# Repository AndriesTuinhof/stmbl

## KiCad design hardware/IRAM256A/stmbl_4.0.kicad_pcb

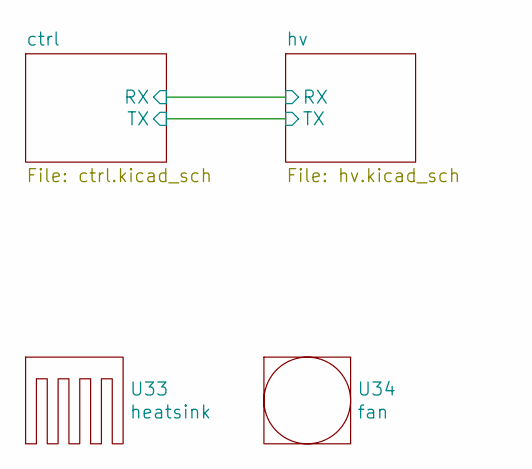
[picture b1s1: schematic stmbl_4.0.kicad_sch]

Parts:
U33: heatsink
U34: fan; Voltage 12V

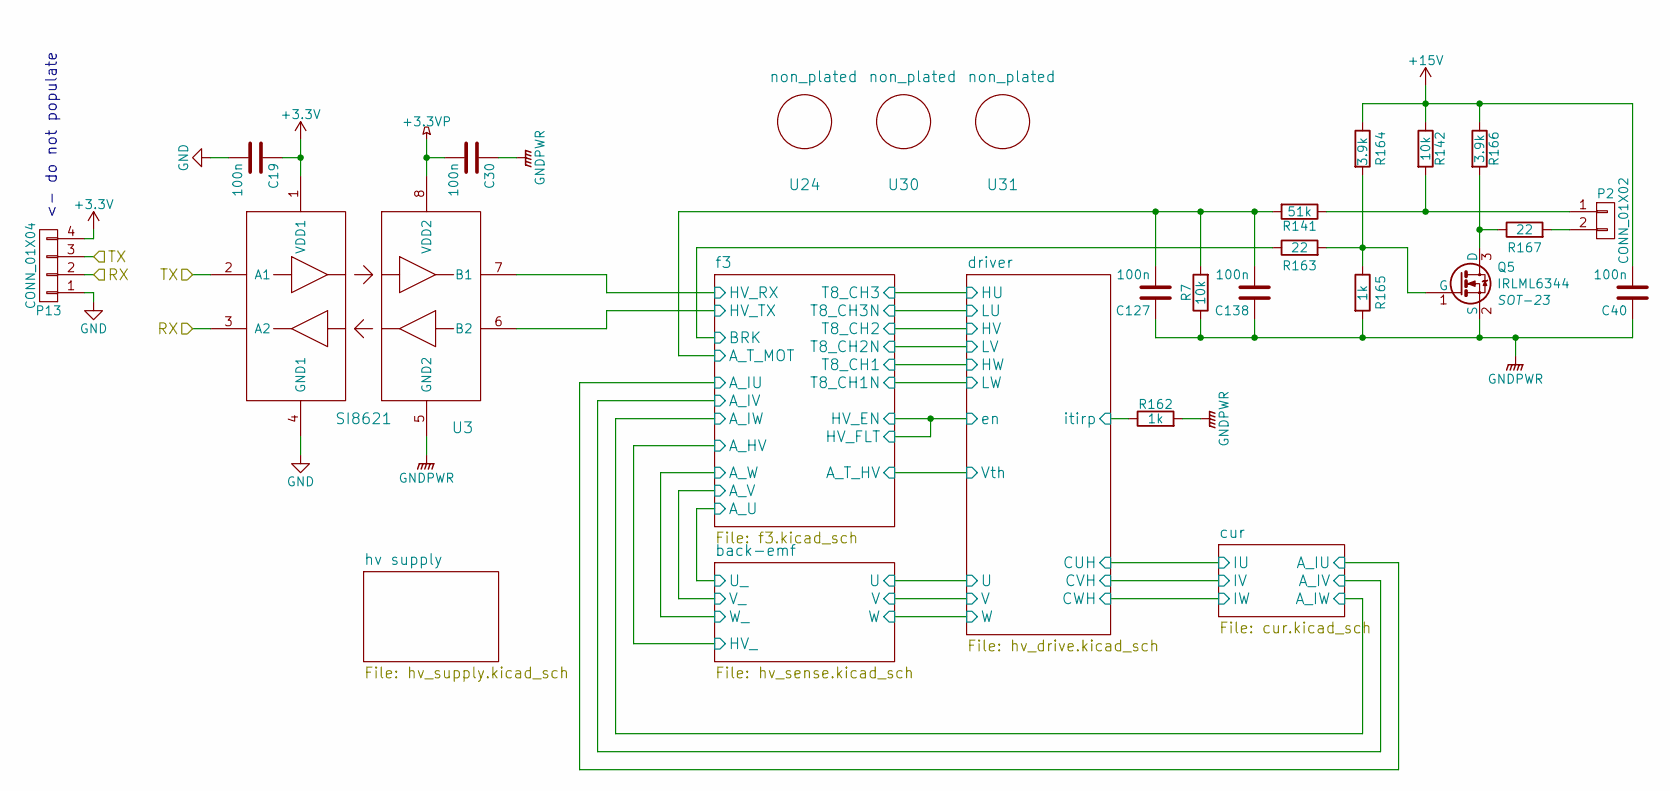
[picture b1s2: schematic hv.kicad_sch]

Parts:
C19, C30, C40, C127, C138: 100n; C_0603; Voltage 50V; Tolerance X5R
P2: CONN_01X02; RM3.5_1x2
P13: CONN_01X04; Socket_Strip_Straight_1x04
Q5: IRLML6344; SOT-23
R7, R142: 10k; R_0603; Tolerance 1%
R141: 51k; R_0603; Tolerance 1%
R162, R165: 1k; R_0603; Tolerance 1%
R163, R167: 22; R_0603; Tolerance 1%
R164, R166: 3.9k; R_0603; Tolerance 1%
U3: SI8621; SOIC-8-N
U24, U30, U31: non_plated; non_plated_3mm

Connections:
+3.3VP: C30.2, U3.8 (VDD2); also elsewhere on the board
+3V3: C19.1, P13.4, U3.1 (VDD1); also elsewhere on the board
+15V: C40.2, R142.1, R164.1, R166.1; also elsewhere on the board
/ctrl/RX: P13.2, U3.3 (A2); also elsewhere on the board
/ctrl/TX: P13.3, U3.2 (A1); also elsewhere on the board
/hv/driver/itirp: R162.1; also elsewhere on the board
/hv/f3/A_T_MOT: C127.2, C138.2, R7.2, R141.2; also elsewhere on the board
/hv/f3/BRK: R163.1; also elsewhere on the board
/hv/f3/HV_RX: U3.7 (B1); also elsewhere on the board
/hv/f3/HV_TX: U3.6 (B2); also elsewhere on the board
GND: C19.2, P13.1, U3.4 (GND1); also elsewhere on the board
GNDPWR: C30.1, C40.1, C127.1, C138.1, Q5.2 (S), R7.1, R162.2, R165.2, U3.5 (GND2); also elsewhere on the board
unnamed: P2.1, R141.1, R142.2
unnamed: P2.2, R167.2
unnamed: Q5.1 (G), R163.2, R164.2, R165.1
unnamed: Q5.3 (D), R166.2, R167.1

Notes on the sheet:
<- do not populate

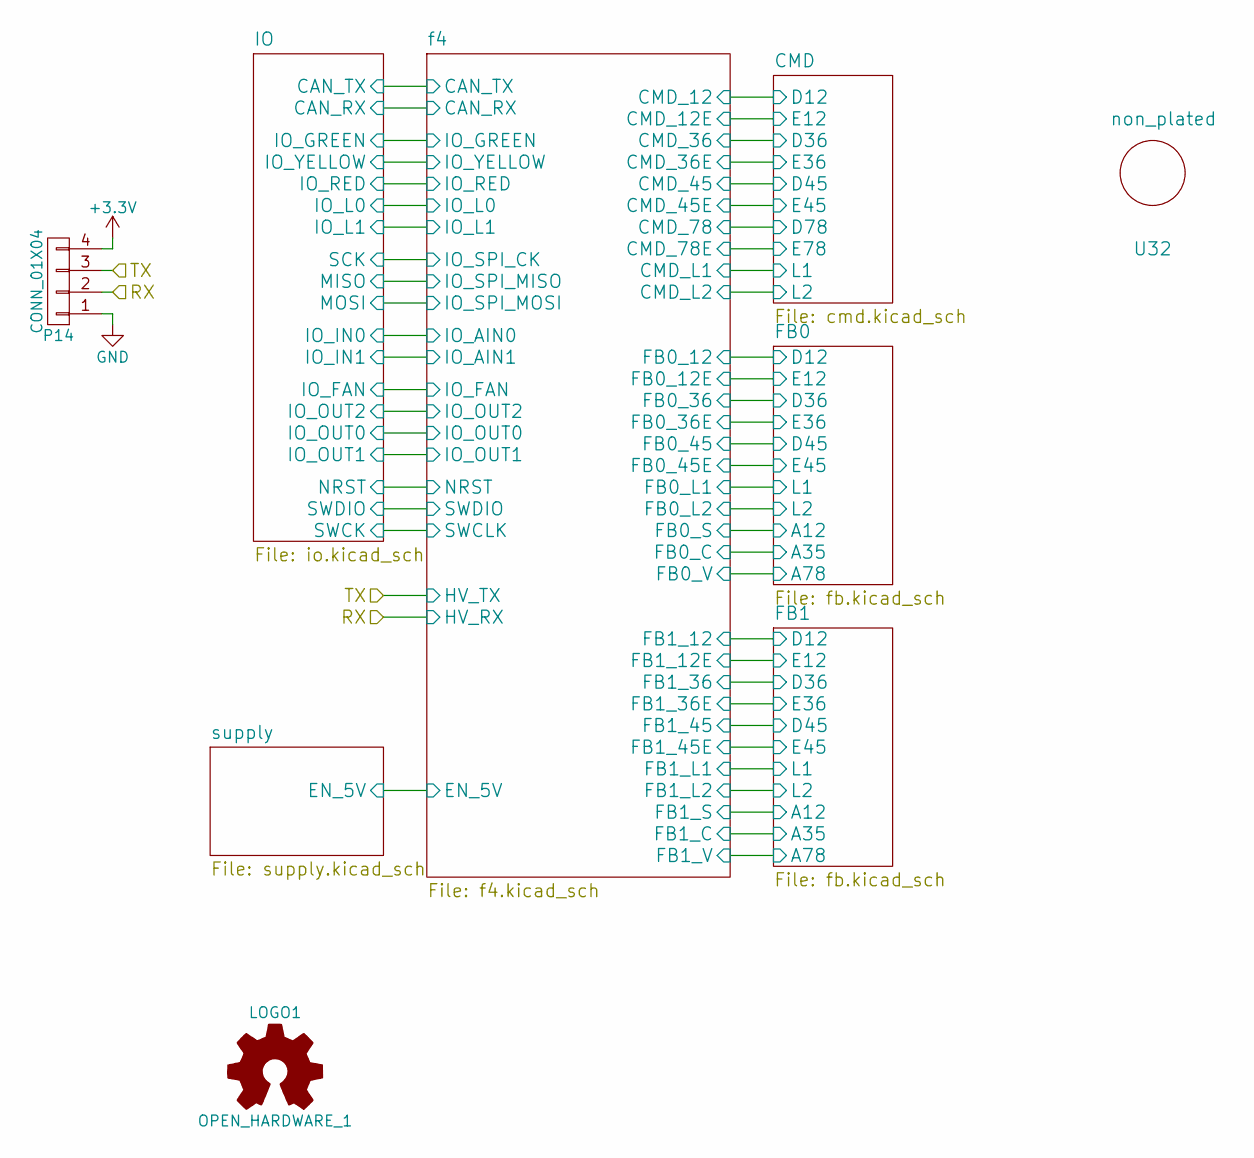
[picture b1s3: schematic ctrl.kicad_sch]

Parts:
LOGO1: OPEN_HARDWARE_1; Symbol_OSHW-Logo_SilkScreen
P14: CONN_01X04; Pin_Header_Angled_1x04
U32: non_plated; non_plated_3mm

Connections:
+3V3: P14.4; also elsewhere on the board
/ctrl/RX: P14.2; also elsewhere on the board
/ctrl/TX: P14.3; also elsewhere on the board
GND: P14.1; also elsewhere on the board

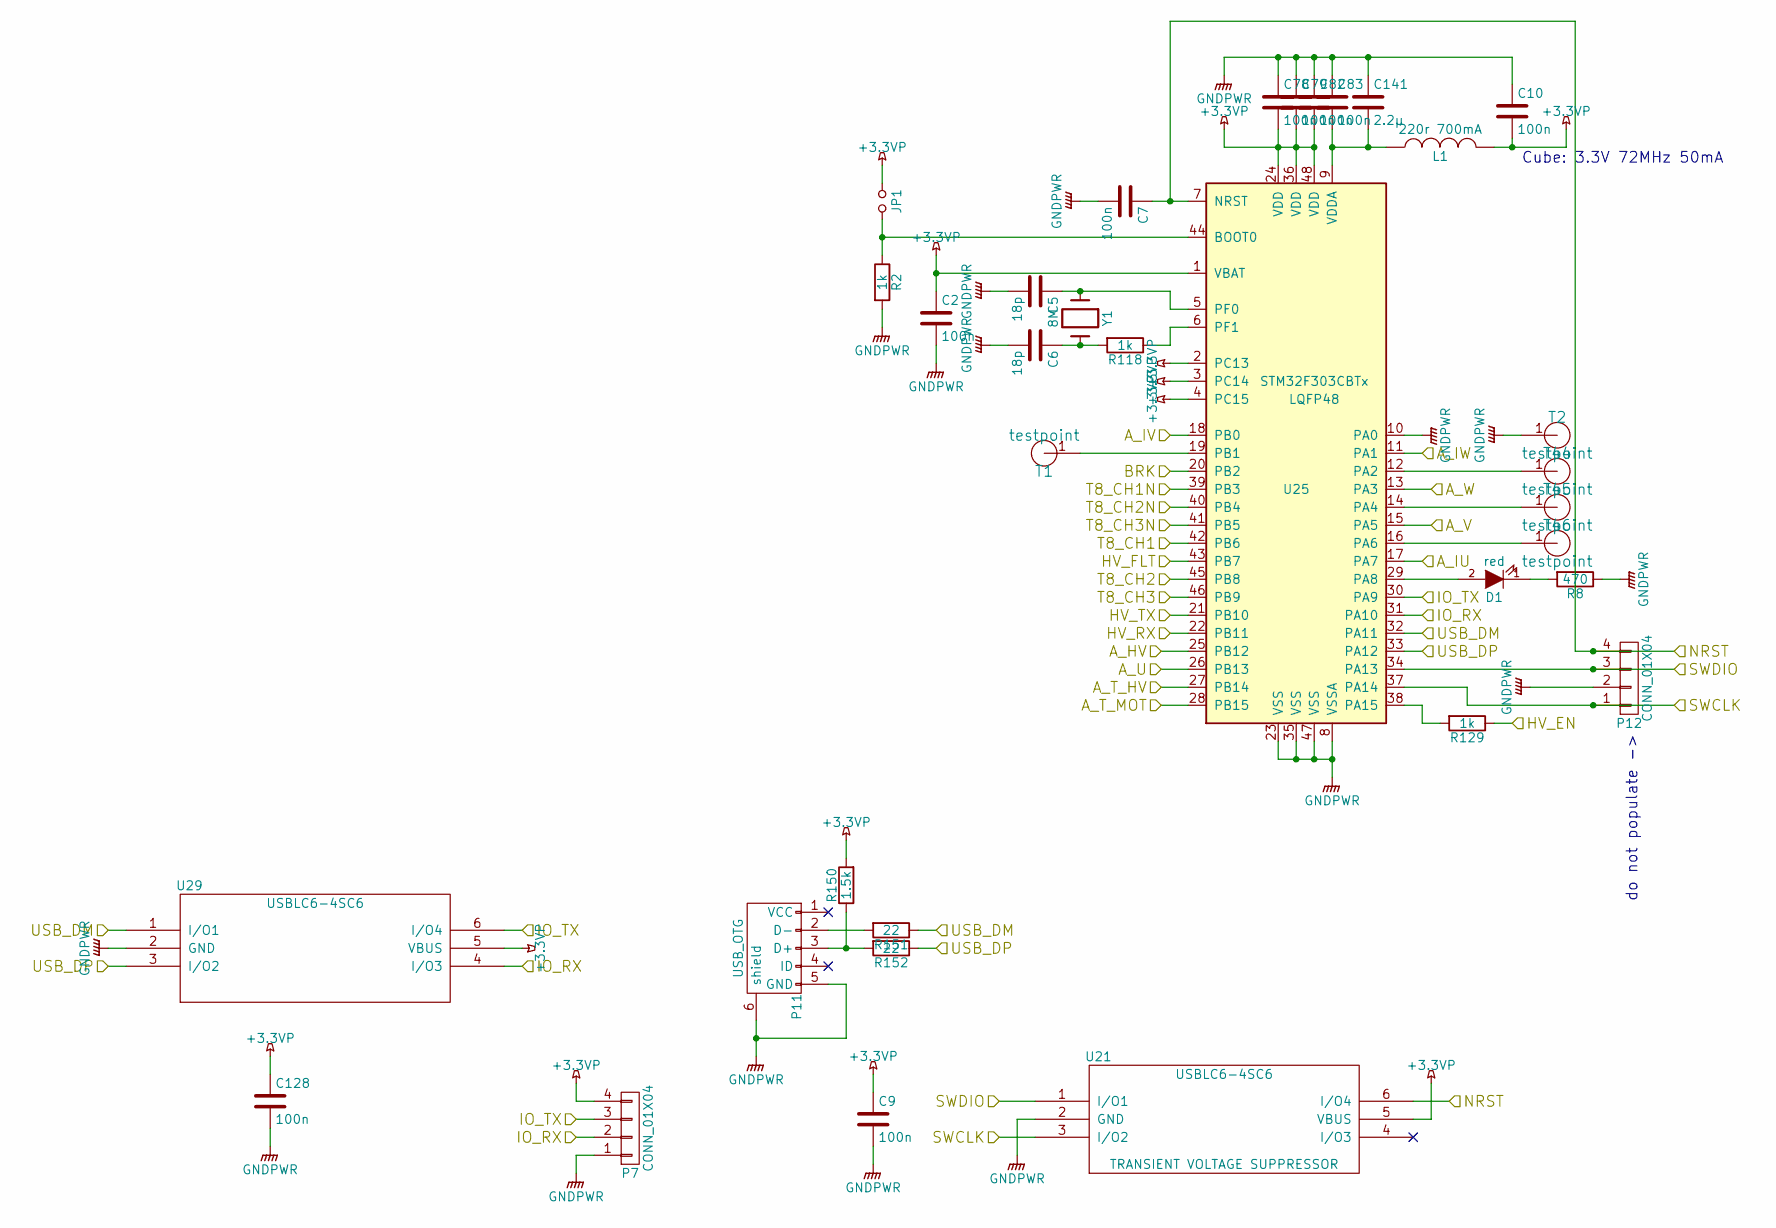
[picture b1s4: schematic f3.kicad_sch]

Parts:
C2, C7, C9, C10, C78, C79, C82, C83, C128: 100n; C_0603; Voltage 50V; Tolerance X5R
C5, C6: 18p; C_0603; Voltage 50V; Tolerance X5R
C141: 2.2µ; C_0603; Voltage 35V; Tolerance X5R
D1: red; LED-0805-SIDE
JP1: Jumper_NO_Small; SOLDER_JUMPER
L1: 220r 700mA; R_0603
P7, P12: CONN_01X04; Pin_Header_Straight_1x04
P11: USB_OTG; USB_Micro-B
R2, R118, R129: 1k; R_0603; Tolerance 1%
R8: 470; R_0603; Tolerance 1%
R150: 1.5k; R_0603; Tolerance 1%
R151, R152: 22; R_0603; Tolerance 1%
T1, T2, T44, T45, T46: testpoint; Measurement_Point_Round-SMD-Pad_Small
U21, U29: USBLC6-4SC6; SOT-23-6
U25: STM32F303CBTx; LQFP48
Y1: 8M; Crystal_SMD_0503_4Pads

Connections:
+3.3VP: C2.1, C9.1, C10.2, C78.2, C79.2, C82.2, C128.1, JP1.1, L1.2, P7.4, R150.2, U21.5 (VBUS), U25.1 (VBAT), U25.2 (PC13), U25.3 (PC14), U25.4 (PC15), U25.24 (VDD), U25.36 (VDD), U25.48 (VDD), U29.5 (VBUS); also elsewhere on the board
/hv/back-emf/HV_: U25.25 (PB12); also elsewhere on the board
/hv/back-emf/U_: U25.26 (PB13); also elsewhere on the board
/hv/back-emf/V_: U25.15 (PA5); also elsewhere on the board
/hv/back-emf/W_: U25.13 (PA3); also elsewhere on the board
/hv/cur/A_IU: U25.17 (PA7); also elsewhere on the board
/hv/cur/A_IV: U25.18 (PB0); also elsewhere on the board
/hv/cur/A_IW: U25.11 (PA1); also elsewhere on the board
/hv/driver/HU: U25.46 (PB9); also elsewhere on the board
/hv/driver/HV: U25.45 (PB8); also elsewhere on the board
/hv/driver/HW: U25.42 (PB6); also elsewhere on the board
/hv/driver/LU: U25.41 (PB5); also elsewhere on the board
/hv/driver/LV: U25.40 (PB4); also elsewhere on the board
/hv/driver/LW: U25.39 (PB3); also elsewhere on the board
/hv/driver/Vth: U25.27 (PB14); also elsewhere on the board
/hv/driver/en: R129.1, U25.43 (PB7); also elsewhere on the board
/hv/f3/A_T_MOT: U25.28 (PB15); also elsewhere on the board
/hv/f3/BRK: U25.20 (PB2); also elsewhere on the board
/hv/f3/HV_RX: U25.22 (PB11); also elsewhere on the board
/hv/f3/HV_TX: U25.21 (PB10); also elsewhere on the board
/hv/f3/IO_RX: P7.2, U25.31 (PA10), U29.4 (I/O3)
/hv/f3/IO_TX: P7.3, U25.30 (PA9), U29.6 (I/O4)
/hv/f3/NRST: C7.1, P12.4, U21.6 (I/O4), U25.7 (NRST)
/hv/f3/SWCLK: P12.1, U21.3 (I/O2), U25.37 (PA14)
/hv/f3/SWDIO: P12.3, U21.1 (I/O1), U25.34 (PA13)
/hv/f3/USB_DM: R151.1, U25.32 (PA11), U29.1 (I/O1)
/hv/f3/USB_DP: R152.1, U25.33 (PA12), U29.3 (I/O2)
GNDPWR: C2.2, C5.2, C6.2, C7.2, C9.2, C10.1, C78.1, C79.1, C82.1, C83.1, C128.2, C141.1, P7.1, P11.5 (GND), P11.6 (shield), P12.2, R2.2, R8.1, T2.1, U21.2 (GND), U25.8 (VSSA), U25.10 (PA0), U25.23 (VSS), U25.35 (VSS), U25.47 (VSS), U29.2 (GND); also elsewhere on the board
unnamed: C5.1, U25.5 (PF0), Y1.1
unnamed: C6.1, R118.2, Y1.2
unnamed: C83.2, C141.2, L1.1, U25.9 (VDDA)
unnamed: D1.1 (K), R8.2
unnamed: D1.2 (A), U25.29 (PA8)
unnamed: JP1.2, R2.1, U25.44 (BOOT0)
unnamed: P11.2 (D-), R151.2
unnamed: P11.3 (D+), R150.1, R152.2
unnamed: R118.1, U25.6 (PF1)
unnamed: R129.2, U25.38 (PA15)
unnamed: T1.1, U25.19 (PB1)
unnamed: T44.1, U25.12 (PA2)
unnamed: T45.1, U25.14 (PA4)
unnamed: T46.1, U25.16 (PA6)

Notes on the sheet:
Cube: 3.3V 72MHz 50mA
do not populate ->

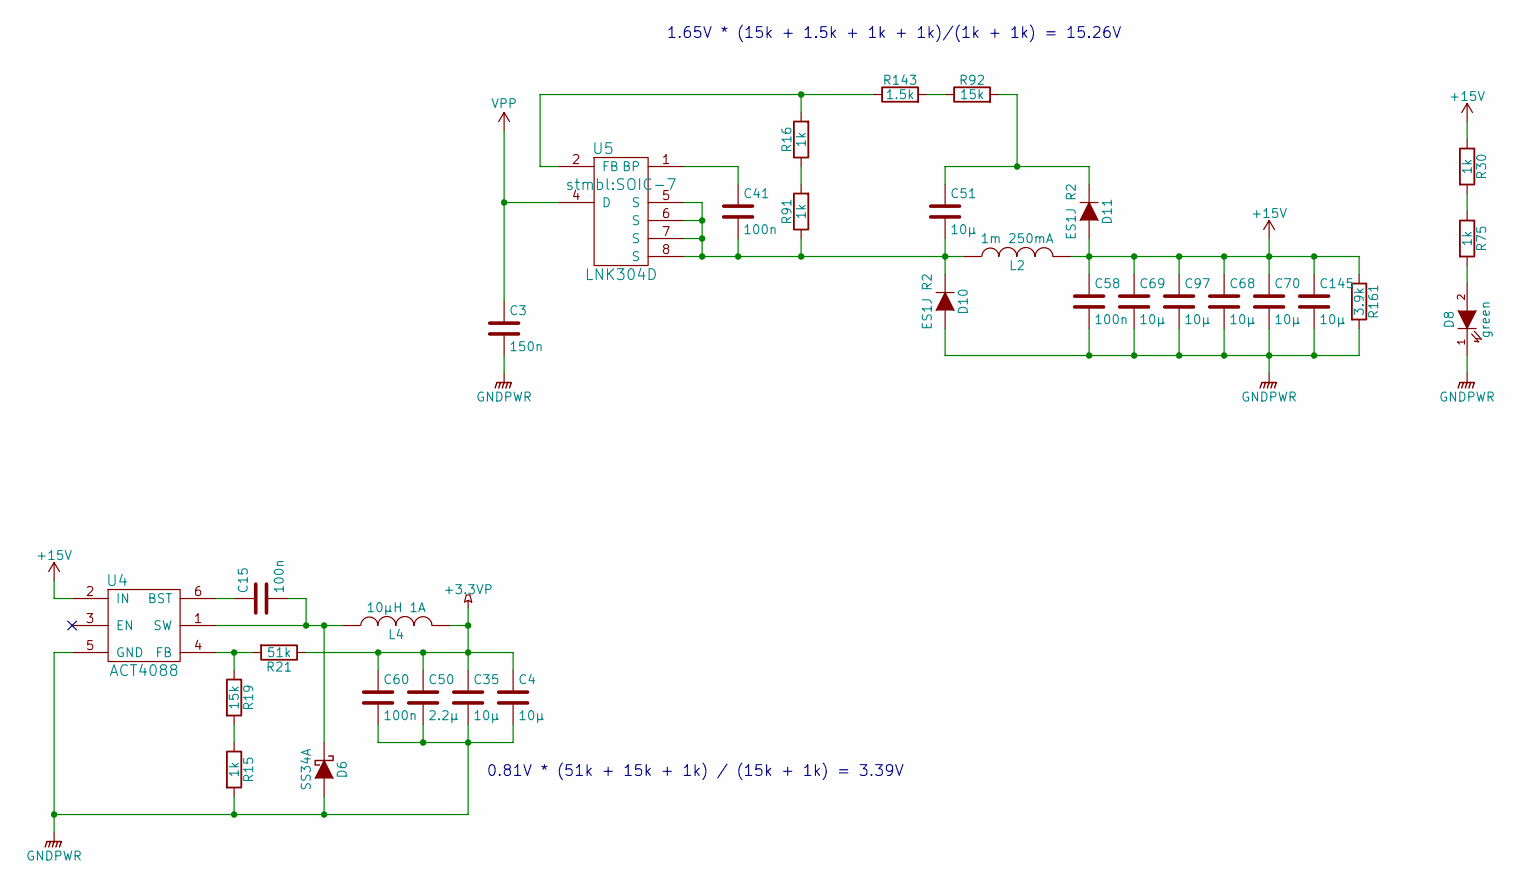
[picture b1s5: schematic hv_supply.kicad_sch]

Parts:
C3: 150n; C_1808; Voltage 500V; Tolerance X7R
C4, C35, C51, C68, C69, C70, C97, C145: 10µ; C_0805; Voltage 25V; Tolerance X5R
C15, C41, C58, C60: 100n; C_0603; Voltage 50V; Tolerance X5R
C50: 2.2µ; C_0603; Voltage 35V; Tolerance X5R
D6: SS34A; SMA_Standard
D8: green; LED-0805-SIDE
D10, D11: ES1J R2; SMA_Standard
L2: 1m 250mA; NPI31W
L4: 10µH 1A; SMD_INDUCTOR_32x25
R15, R16, R30, R75, R91: 1k; R_0603; Tolerance 1%
R19, R92: 15k; R_0603; Tolerance 1%
R21: 51k; R_0603; Tolerance 1%
R143: 1.5k; R_0603; Tolerance 1%
R161: 3.9k; R_0603; Tolerance 1%
U4: ACT4088; SOT-23-6
U5: LNK304D; SOIC-7

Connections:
+3.3VP: C4.1, C35.1, C50.1, C60.1, L4.2, R21.1; also elsewhere on the board
+15V: C58.1, C68.1, C69.1, C70.1, C97.1, C145.1, D11.2 (A), L2.2, R30.1, R161.1, U4.2 (IN); also elsewhere on the board
GNDPWR: C3.2, C4.2, C35.2, C50.2, C58.2, C60.2, C68.2, C69.2, C70.2, C97.2, C145.2, D6.2 (A), D8.1 (K), D10.2 (A), R15.2, R161.2, U4.5 (GND); also elsewhere on the board
unnamed: C15.1, U4.6 (BST)
unnamed: C15.2, D6.1 (K), L4.1, U4.1 (SW)
unnamed: C41.1, U5.1 (BP)
unnamed: C41.2, C51.2, D10.1 (K), L2.1, R91.1, U5.5 (S), U5.6 (S), U5.7 (S), U5.8 (S)
unnamed: C51.1, D11.1 (K), R92.2
unnamed: D8.2 (A), R75.2
unnamed: R15.1, R19.2
unnamed: R16.1, R91.2
unnamed: R19.1, R21.2, U4.4 (FB)
unnamed: R30.2, R75.1
unnamed: R16.2, R143.1, U5.2 (FB)
unnamed: R92.1, R143.2
VPP: C3.1, U5.4 (D); also elsewhere on the board

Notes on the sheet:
0.81V * (51k + 15k + 1k) / (15k + 1k) = 3.39V
1.65V * (15k + 1.5k + 1k + 1k)/(1k + 1k) = 15.26V

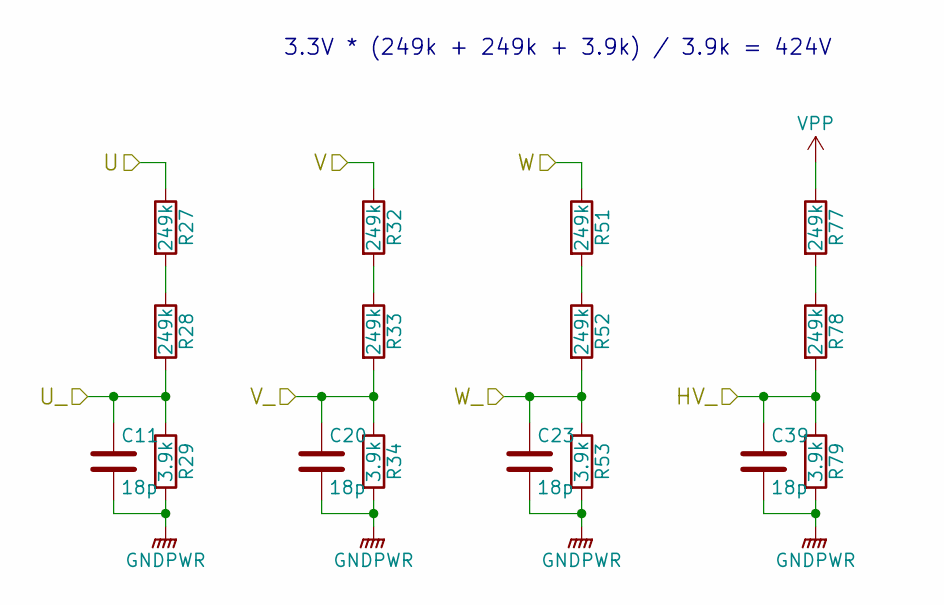
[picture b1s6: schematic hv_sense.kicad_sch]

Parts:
C11, C20, C23, C39: 18p; C_0603; Voltage 50V; Tolerance X5R
R27, R28, R32, R33, R51, R52, R77, R78: 249k; R_1206; Voltage 200V; Tolerance 1%
R29, R34, R53, R79: 3.9k; R_0603; Tolerance 1%

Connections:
/hv/back-emf/HV_: C39.1, R78.2, R79.1; also elsewhere on the board
/hv/back-emf/U: R27.1; also elsewhere on the board
/hv/back-emf/U_: C11.1, R28.2, R29.1; also elsewhere on the board
/hv/back-emf/V: R32.1; also elsewhere on the board
/hv/back-emf/V_: C20.1, R33.2, R34.1; also elsewhere on the board
/hv/back-emf/W: R51.1; also elsewhere on the board
/hv/back-emf/W_: C23.1, R52.2, R53.1; also elsewhere on the board
GNDPWR: C11.2, C20.2, C23.2, C39.2, R29.2, R34.2, R53.2, R79.2; also elsewhere on the board
unnamed: R27.2, R28.1
unnamed: R32.2, R33.1
unnamed: R51.2, R52.1
unnamed: R77.2, R78.1
VPP: R77.1; also elsewhere on the board

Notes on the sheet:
3.3V * (249k + 249k + 3.9k) / 3.9k = 424V

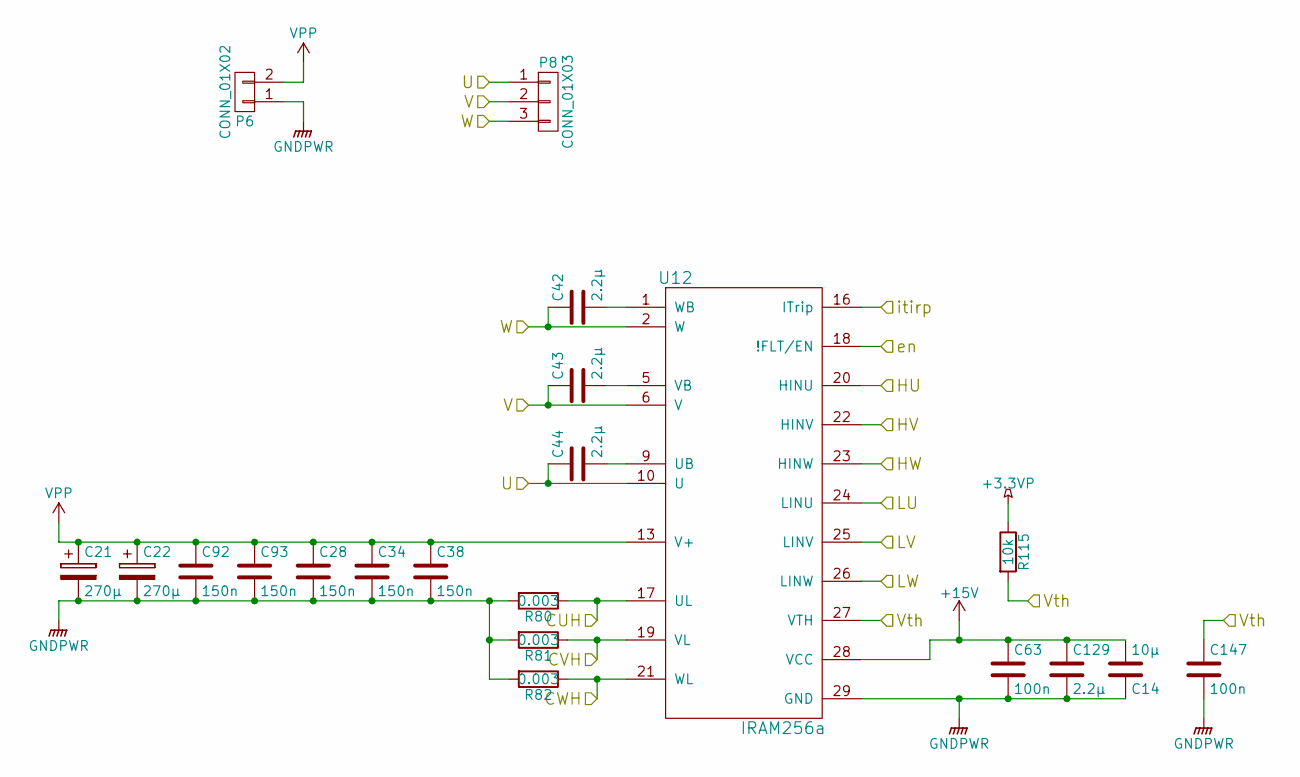
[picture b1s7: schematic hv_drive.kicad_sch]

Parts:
C14: 10µ; C_0805; Voltage 25V; Tolerance X5R
C21, C22: 270µ; C_Radial_D26_L45_P10; Voltage 400V
C28, C34, C38, C92, C93: 150n; C_1808; Voltage 500V; Tolerance X7R
C42, C43, C44, C129: 2.2µ; C_0603; Voltage 35V; Tolerance X5R
C63, C147: 100n; C_0603; Voltage 50V; Tolerance X5R
P6: CONN_01X02; RM5.08_1x2
P8: CONN_01X03; RM5.08_1x3
R80, R81, R82: 0.003; R_2512; Tolerance 1%
R115: 10k; R_0603; Tolerance 1%
U12: IRAM256a; IRAM256

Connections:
+3.3VP: R115.1; also elsewhere on the board
+15V: C14.2, C63.1, C129.1, U12.28 (VCC); also elsewhere on the board
/hv/back-emf/U: C44.1, P8.1, U12.10 (U); also elsewhere on the board
/hv/back-emf/V: C43.1, P8.2, U12.6 (V); also elsewhere on the board
/hv/back-emf/W: C42.1, P8.3, U12.2 (W); also elsewhere on the board
/hv/cur/IU: R80.1, U12.17 (UL); also elsewhere on the board
/hv/cur/IV: R81.1, U12.19 (VL); also elsewhere on the board
/hv/cur/IW: R82.1, U12.21 (WL); also elsewhere on the board
/hv/driver/HU: U12.20 (HINU); also elsewhere on the board
/hv/driver/HV: U12.22 (HINV); also elsewhere on the board
/hv/driver/HW: U12.23 (HINW); also elsewhere on the board
/hv/driver/LU: U12.24 (LINU); also elsewhere on the board
/hv/driver/LV: U12.25 (LINV); also elsewhere on the board
/hv/driver/LW: U12.26 (LINW); also elsewhere on the board
/hv/driver/Vth: C147.1, R115.2, U12.27 (VTH); also elsewhere on the board
/hv/driver/en: U12.18 (!FLT/EN); also elsewhere on the board
/hv/driver/itirp: U12.16 (ITrip); also elsewhere on the board
GNDPWR: C14.1, C21.2, C22.2, C28.2, C34.2, C38.2, C63.2, C92.2, C93.2, C129.2, C147.2, P6.1, R80.2, R81.2, R82.2, U12.29 (GND); also elsewhere on the board
unnamed: C42.2, U12.1 (WB)
unnamed: C43.2, U12.5 (VB)
unnamed: C44.2, U12.9 (UB)
VPP: C21.1, C22.1, C28.1, C34.1, C38.1, C92.1, C93.1, P6.2, U12.13 (V+); also elsewhere on the board

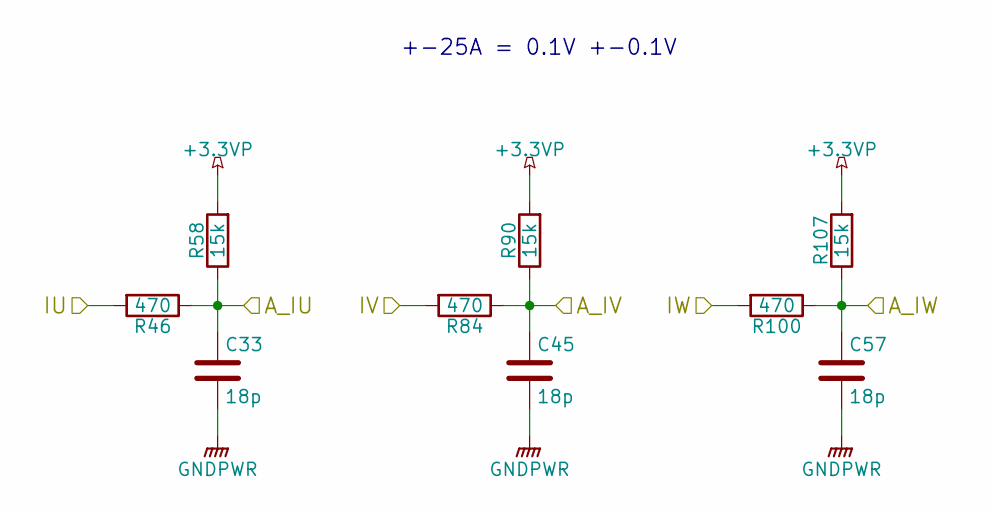
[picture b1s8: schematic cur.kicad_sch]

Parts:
C33, C45, C57: 18p; C_0603; Voltage 50V; Tolerance X5R
R46, R84, R100: 470; R_0603; Tolerance 1%
R58, R90, R107: 15k; R_0603; Tolerance 1%

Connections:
+3.3VP: R58.2, R90.2, R107.2; also elsewhere on the board
/hv/cur/A_IU: C33.1, R46.1, R58.1; also elsewhere on the board
/hv/cur/A_IV: C45.1, R84.1, R90.1; also elsewhere on the board
/hv/cur/A_IW: C57.1, R100.1, R107.1; also elsewhere on the board
/hv/cur/IU: R46.2; also elsewhere on the board
/hv/cur/IV: R84.2; also elsewhere on the board
/hv/cur/IW: R100.2; also elsewhere on the board
GNDPWR: C33.2, C45.2, C57.2; also elsewhere on the board

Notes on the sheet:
+-25A = 0.1V +-0.1V

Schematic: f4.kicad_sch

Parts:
C1, C16, C29, C61, C66, C67, C77, C80, C84, C85, C86, C87, C89, C119: 100n; C_0603; Voltage 50V; Tolerance X5R
C31, C32: 18p; C_0603; Voltage 50V; Tolerance X5R
C64, C81: 1n; C_0603; Voltage 50V; Tolerance X5R
C65, C88, C90: 2.2µ; C_0603; Voltage 35V; Tolerance X5R
JP9: Jumper_NO_Small; SOLDER_JUMPER
L3: 220r 700mA; R_0603
P1: USB_OTG; USB_Micro-B
R1: 120; R_0603; Tolerance 1%
R61, R117, R121, R122, R153: 1k; R_0603; Tolerance 1%
R116: 10k; R_0603; Tolerance 1%
U1, U20, U22, U23: USBLC6-4SC6; SOT-23-6
U26: STM32F405VG; TQFP100
Y2: 8M; Crystal_SMD_0503_4Pads

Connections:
+3V3: C16.2, C67.1, C77.2, C80.2, C84.2, C85.2, C86.2, C87.2, C89.2, JP9.1, L3.2, U1.5 (VBUS), U23.5 (VBUS), U26.6 (VBAT), U26.11 (VDD), U26.19 (VDD), U26.28 (VDD), U26.50 (VDD), U26.75 (VDD), U26.100 (VDD); also elsewhere on the board
+5V: C61.1, C66.1, U20.5 (VBUS), U22.5 (VBUS); also elsewhere on the board
+5VA: R121.1; also elsewhere on the board
+24V: R116.1; also elsewhere on the board
/ctrl/CMD/D12: U22.4 (I/O3), U26.69 (PA10/USART1_RX/TIM1_CH3/OTG_FS_ID/EVENT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), U26.77 (PA15/JTDI/SPI3_NSS/I2S3_WS/TIM2_CH1_ETR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), U26.90 (PB4/NJTRST/SPI3_MISO/TIM3_CH1/SPI1_MISO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); also elsewhere on the board
/ctrl/CMD/D36: U22.1 (I/O1), U26.23 (PA0/WKUP/USART2_CTS/UART4_TX/TIM2_CH1_E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), U26.67 (PA8/MCO1/USART1_CK/TIM1_CH1/I2C3_SCL/OT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), U26.89 (PB3/JTDO/TRACESWO/SPI3_SCK/I2S3_CK/TIM2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); also elsewhere on the board
/ctrl/CMD/D45: U22.6 (I/O4), U26.68 (PA9/USART1_TX/TIM1_CH2/I2C3_SMBA/EVENTO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), U26.91 (PB5/I2C1_SMBA/CAN2_RX/OTG_HS_ULPI_D7/TI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); also elsewhere on the board
/ctrl/CMD/D78: U26.95 (PB8/TIM4_CH3/SDIO_D4/TIM10_CH1/I2C1_SCL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); also elsewhere on the board
/ctrl/CMD/E12: U26.92 (PB6/I2C1_SCL/TIM4_CH1/CAN2_TX/USART1_TX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); also elsewhere on the board
/ctrl/CMD/E36: U26.93 (PB7/I2C1_SDA/FSMC_NL/USART1_RX/TIM4_CH2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); also elsewhere on the board
/ctrl/CMD/E45: U26.96 (PB9/SPI2_NSS/I2S2_WS/TIM4_CH4/TIM11_CH1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); also elsewhere on the board
/ctrl/CMD/E78: U26.37 (PB2/BOOT1/EVENTOUT); also elsewhere on the board
/ctrl/CMD/L1: U26.88 (PD7/USART2_CK/FSMC_NE1/FSMC_NCE2/EVENTO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); also elsewhere on the board
/ctrl/CMD/L2: U26.87 (PD6/FSMC_NWAIT/USART2_RX/EVENTOUT); also elsewhere on the board
/ctrl/FB0/A12: U26.31 (PA6/SPI1_MISO/TIM8_BKIN/TIM13_CH1/TIM3_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); also elsewhere on the board
/ctrl/FB0/A35: U26.32 (PA7/SPI1_MOSI/TIM8_CH1N/TIM14_CH1/TIM3_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); also elsewhere on the board
/ctrl/FB0/A78: U23.1 (I/O1), U26.17 (PC2/SPI2_MISO/OTG_HS_ULPI_DIR/I2S2ext_S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); also elsewhere on the board
/ctrl/FB0/D12: U26.59 (PD12/FSMC_ALE/FSMC_A17/TIM4_CH1/USART3_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), U26.64 (PC7/I2S3_MCK/TIM8_CH2/SDIO_D7/USART6_RX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), U26.79 (PC11/UART4_RX/SPI3_MISO/SDIO_D3/USART3_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); also elsewhere on the board
/ctrl/FB0/D36: U26.60 (PD13/FSMC_A18/TIM4_CH2/EVENTOUT), U26.65 (PC8/TIM8_CH3/SDIO_D0/TIM3_CH3/USART6_CK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), U26.78 (PC10/SPI3_SCK/I2S3_CK/UART4_TX/SDIO_D2/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); also elsewhere on the board
/ctrl/FB0/D45: U26.61 (PD14/FSMC_D0/TIM4_CH3/EVENTOUT/_EVENTOUT), U26.63 (PC6/I2S2_MCK/TIM8_CH1/SDIO_D6/USART6_TX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), U26.80 (PC12/UART5_TX/SDIO_CK/SPI3_MOSI/I2S3_SD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); also elsewhere on the board
/ctrl/FB0/E12: U26.58 (PD11/FSMC_CLE/FSMC_A16/USART3_CTS/EVENT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); also elsewhere on the board
/ctrl/FB0/E36: U26.57 (PD10/FSMC_D15/USART3_CK/EVENTOUT); also elsewhere on the board
/ctrl/FB0/E45: U26.62 (PD15/FSMC_D1/TIM4_CH4/EVENTOUT); also elsewhere on the board
/ctrl/FB0/L1: U26.55 (PD8/FSMC_D13/USART3_TX/EVENTOUT); also elsewhere on the board
/ctrl/FB0/L2: U26.56 (PD9/FSMC_D14/USART3_RX/EVENTOUT); also elsewhere on the board
/ctrl/FB1/A12: U26.29 (PA4/SPI1_NSS/SPI3_NSS/USART2_CK/OTG_HS_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); also elsewhere on the board
/ctrl/FB1/A35: U26.30 (PA5/SPI1_SCK/OTG_HS_ULPI_CK/TIM2_CH1_ET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); also elsewhere on the board
/ctrl/FB1/A78: U23.6 (I/O4), U26.18 (PC3/SPI2_MOSI/I2S2_SD/OTG_HS_ULPI_NXT/E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); also elsewhere on the board
/ctrl/FB1/D12: U26.40 (PE9/FSMC_D6/TIM1_CH1/EVENTOUT), U26.48 (PB11/I2C2_SDA/USART3_RX/OTG_HS_ULPI_D4/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), U26.53 (PB14/SPI2_MISO/TIM1_CH2N/TIM12_CH1/OTG_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); also elsewhere on the board
/ctrl/FB1/D36: U26.42 (PE11/FSMC_D8/TIM1_CH2/EVENTOUT), U26.51 (PB12/SPI2_NSS/I2S2_WS/I2C2_SMBA/USART3_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), U26.52 (PB13/SPI2_SCK/I2S2_CK/USART3_CTS/TIM1_C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); also elsewhere on the board
/ctrl/FB1/D45: U26.44 (PE13/FSMC_D10/TIM1_CH3/EVENTOUT), U26.47 (PB10/SPI2_SCK/I2S2_CK/I2C2_SCL/USART3_T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), U26.54 (PB15/SPI2_MOSI/I2S2_SD/TIM1_CH3N/TIM8_C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); also elsewhere on the board
/ctrl/FB1/E12: U26.41 (PE10/FSMC_D7/TIM1_CH2N/EVENTOUT); also elsewhere on the board
/ctrl/FB1/E36: U26.43 (PE12/FSMC_D9/TIM1_CH3N/EVENTOUT); also elsewhere on the board
/ctrl/FB1/E45: U26.45 (PE14/FSMC_D11/TIM1_CH4/EVENTOUT); also elsewhere on the board
/ctrl/FB1/L1: U26.38 (PE7/FSMC_D4/TIM1_ETR/EVENTOUT); also elsewhere on the board
/ctrl/FB1/L2: U26.39 (PE8/FSMC_D5/TIM1_CH1N/EVENTOUT); also elsewhere on the board
/ctrl/IO/CAN_RX: U20.3 (I/O2), U26.81 (PD0/FSMC_D2/CAN1_RX/EVENTOUT); also elsewhere on the board
/ctrl/IO/CAN_TX: U20.6 (I/O4), U26.82 (PD1/FSMC_D3/CAN1_TX/EVENTOUT); also elsewhere on the board
/ctrl/IO/IO_FAN: U26.2 (PE3/TRACED0/FSMC_A19/EVENTOUT); also elsewhere on the board
/ctrl/IO/IO_GREEN: U26.86 (PD5/FSMC_NWE/USART2_TX/EVENTOUT); also elsewhere on the board
/ctrl/IO/IO_IN0: U23.4 (I/O3), U26.15 (PC0/OTG_HS_ULPI_STP/EVENTOUT); also elsewhere on the board
/ctrl/IO/IO_IN1: U23.3 (I/O2), U26.16 (PC1/_EVENTOUT); also elsewhere on the board
/ctrl/IO/IO_L0: U26.98 (PE1/FSMC_NBL1/EVENTOUT); also elsewhere on the board
/ctrl/IO/IO_L1: U26.97 (PE0/TIM4_ETR/FSMC_NBL0/EVENTOUT); also elsewhere on the board
/ctrl/IO/IO_OUT0: U26.3 (PE4/TRACED1/FSMC_A20/EVENTOUT); also elsewhere on the board
/ctrl/IO/IO_OUT1: U26.4 (PE5/TRACED2/FSMC_A21/TIM9_CH1/EVENTOUT); also elsewhere on the board
/ctrl/IO/IO_OUT2: U26.5 (PE6/TRACED3_/_FSMC_A22/TIM9_CH2/EVENTOUT); also elsewhere on the board
/ctrl/IO/IO_RED: U26.84 (PD3/FSMC_CLK/USART2_CTS/EVENTOUT); also elsewhere on the board
/ctrl/IO/IO_YELLOW: U26.85 (PD4/FSMC_NOE/USART2_RTS/EVENTOUT); also elsewhere on the board
/ctrl/IO/NRST: C29.2, U22.3 (I/O2), U26.14 (NRST); also elsewhere on the board
/ctrl/IO/SWCK: U20.4 (I/O3), U26.76 (PA14/JTCK/SWCLK/EVENTOUT); also elsewhere on the board
/ctrl/IO/SWDIO: U20.1 (I/O1), U26.72 (PA13/JTMS/SWDIO/EVENTOUT); also elsewhere on the board
/ctrl/RX: U26.26 (PA3/USART2_RX/TIM5_CH4/TIM9_CH2/TIM2_CH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); also elsewhere on the board
/ctrl/TX: U26.25 (PA2/USART2_TX/TIM5_CH3/TIM9_CH1/TIM2_CH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); also elsewhere on the board
/ctrl/f4/A_5V: C81.1, R121.2, R122.1, U26.24 (PA1/USART2_RTS/UART4_RX/TIM5_CH2/TIMM2_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)
/ctrl/f4/A_24V: C64.1, R116.2, R117.1, U26.36 (PB1/TIM3_CH4/TIM8_CH3N/OTG_HS_ULPI_D2/O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)
/ctrl/f4/EN_5V: U26.7 (PC13/EVENTOUT); also elsewhere on the board
GND: C1.2, C16.1, C29.1, C31.2, C32.2, C61.2, C64.2, C65.1, C66.2, C67.2, C77.1, C80.1, C81.2, C84.1, C85.1, C86.1, C87.1, C88.2, C89.1, C90.2, C119.1, P1.5 (GND), R1.2, R61.1, R117.2, R122.2, U1.2 (GND), U20.2 (GND), U22.2 (GND), U23.2 (GND), U26.1 (PE2/TRACECLK/FSMC_A23/EVENTOUT), U26.8 (PC14/OSC32_IN/EVENTOUT), U26.9 (PC15/OSC32_OUT/EVENTOUT), U26.10 (VSS), U26.20 (VSSA), U26.27 (VSS), U26.33 (PC4/EVENTOUT), U26.34 (PC5/EVENTOUT), U26.35 (PB0/TIM3_CH3/TIM8_CH2N/OTG_HS_ULPI_D1/T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), U26.46 (PE15/FSMC_D12/TIM1_BKIN/EVENTOUT), U26.66 (PC9/I2S_CKIN/MCO2/TIM8_CH4/SDIO_D1/I2C3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), U26.74 (VSS), U26.83 (PD2/TIM3_ETR/UART5_RX/SDIO_CMD/EVENTOUT), U26.99 (VSS); also elsewhere on the board
unnamed: C1.1, P1.6 (shield), R1.1
unnamed: C31.1, U26.12 (PH0/OSC_IN/EVENTOUT), Y2.1
unnamed: C32.1, R153.2, Y2.2
unnamed: C88.1, U26.49 (VCAP_1)
unnamed: C90.1, U26.73 (VCAP_2)
unnamed: C65.2, C119.2, L3.1, U26.21 (VREF+), U26.22 (VDDA)
unnamed: JP9.2, R61.2, U26.94 (BOOT0)
unnamed: P1.2 (D-), U1.1 (I/O1), U26.70 (PA11/USART1_CTS/CAN1_RX/TIM1_CH4_/OTG_F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)
unnamed: P1.3 (D+), U1.3 (I/O2), U26.71 (PA12/USART1_RTS/CAN1_TX/TIM1_ETR/OTG_FS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)
unnamed: R153.1, U26.13 (PH1/OSC_OUT/EVENTOUT)

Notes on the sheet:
Cube: 3.3V 168MHz 75mA

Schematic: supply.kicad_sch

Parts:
C8, C18, C62, C101, C102, C133, C134, C135, C136, C137, C139, C140, C142, C144: 2.2µ; C_0603; Voltage 35V; Tolerance X5R
C96, C99, C103, C104, C105, C106, C107, C108, C120, C121, C122: 100n; C_0603; Voltage 50V; Tolerance X5R
C109, C110, C111, C123, C124, C131, C132: 10µ; C_0805; Voltage 25V; Tolerance X5R
C143: 22µ; C_Radial_D6.5_L11_P2.5; Voltage 50V
D9, D12, D13: SS34A; SMA_Standard
D22: SMAJ24A TVS 24V; SMA_Standard
D24: green; LED-0805-SIDE
JP4: Jumper_NO_Small; SOLDER_JUMPER
JP6: JUMPER3_NC; SOLDER_JUMPER_3_NC
L5, L12: 4.7µH 1.5A; SMD_INDUCTOR_32x25
L6: 10µH 1A; SMD_INDUCTOR_32x25
P3: CONN_01X02; RM3.5_1x2
R35, R132, R155, R156, R157, R158: 10k; R_0603; Tolerance 1%
R59, R144, R146, R149: 3.9k; R_0603; Tolerance 1%
R60, R97, R133: 51k; R_0603; Tolerance 1%
R145: 1k; R_0603; Tolerance 1%
R154, R159, R160: 22; R_0603; Tolerance 1%
U2: zldo1117; SOT-223
U13, U27, U28: ACT4088; SOT-23-6

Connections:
+3V3: C18.1, C99.1, C131.1, JP6.3, U2.2 (VO); also elsewhere on the board
+5F: C122.1, C123.1, C124.1, C134.1, JP4.1, L12.2, R144.1; also elsewhere on the board
+5V: C8.1, C96.1, C107.1, C109.1, C111.1, C135.1, JP4.2, JP6.1, L5.2, R145.1, U2.3 (VI); also elsewhere on the board
+5VA: JP6.2; also elsewhere on the board
+12V: C108.1, C110.1, C132.1, C136.1, L6.2, R146.1; also elsewhere on the board
+24V: C102.1, C103.1, C104.1, C120.1, C133.1, C137.1, C143.1, D22.1 (K), D24.2 (A), P3.1, R154.1, R155.1, R156.1, R157.1, R158.1, R159.1, R160.1, U13.2 (IN), U27.2 (IN), U28.2 (IN); also elsewhere on the board
/ctrl/f4/EN_5V: U28.3 (EN); also elsewhere on the board
GND: C8.2, C18.2, C62.2, C96.2, C99.2, C101.2, C102.2, C103.2, C104.2, C107.2, C108.2, C109.2, C110.2, C111.2, C120.2, C122.2, C123.2, C124.2, C131.2, C132.2, C133.2, C134.2, C135.2, C136.2, C137.2, C139.2, C140.2, C142.2, C143.2, C144.2, D9.2 (A), D12.2 (A), D13.2 (A), D22.2 (A), P3.2, R35.2, R59.2, R132.2, R149.2, R155.2, R156.2, R157.2, R158.2, U2.1 (GND), U13.5 (GND), U27.5 (GND), U28.5 (GND); also elsewhere on the board
unnamed: C62.1, C101.1, R159.2
unnamed: C105.1, U13.6 (BST)
unnamed: C105.2, D9.1 (K), L5.1, U13.1 (SW)
unnamed: C106.1, U27.6 (BST)
unnamed: C106.2, D12.1 (K), L6.1, U27.1 (SW)
unnamed: C121.1, U28.6 (BST)
unnamed: C121.2, D13.1 (K), L12.1, U28.1 (SW)
unnamed: C139.1, C140.1, C142.1, C144.1, R154.2, R160.2
unnamed: D24.1 (K), R149.1
unnamed: R35.1, R60.2, U13.4 (FB)
unnamed: R59.1, R97.2, U27.4 (FB)
unnamed: R132.1, R133.2, U28.4 (FB)
unnamed: R133.1, R144.2
unnamed: R60.1, R145.2
unnamed: R97.1, R146.2

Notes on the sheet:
0.81V * (51k + 3.9k + 3.9k) / 3.9k = 12.21V
0.81V * (51k + 3.9k + 10k) / 10k = 5.25V
0.81V * (51k + 1k + 10k) / 10k = 5.02V
FB and FAN
CPU, IO and analog
FB and RS485

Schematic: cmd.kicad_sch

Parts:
C17, C53, C54, C55, C56, C112: 100n; C_0603; Tolerance X5R; Voltage 50V
J3: RJ45_LED
L7: 220r 700mA; R_0603
P15: CONN_01X02; RM3.5_1x2
R17, R18: 470; R_0603; Tolerance 1%
R31: 120; R_0603; Tolerance 1%
R62, R64, R65, R67, R68, R70, R71, R73: 10k; R_0603; Tolerance 1%
R63, R66, R69, R72, R101, R102, R103, R104: 1k; R_0603; Tolerance 1%
U8, U9, U10, U11: SN65176B; SO-8

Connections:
+5F: C112.1, L7.2; also elsewhere on the board
/ctrl/CMD/D12: U8.1 (RO), U8.4 (DI); also elsewhere on the board
/ctrl/CMD/D36: U9.1 (RO), U9.4 (DI); also elsewhere on the board
/ctrl/CMD/D45: U10.1 (RO), U10.4 (DI); also elsewhere on the board
/ctrl/CMD/D78: U11.1 (RO), U11.4 (DI); also elsewhere on the board
/ctrl/CMD/E12: R101.1, U8.2 (~RE), U8.3 (DE); also elsewhere on the board
/ctrl/CMD/E36: R102.1, U9.2 (~RE), U9.3 (DE); also elsewhere on the board
/ctrl/CMD/E45: R103.1, U10.2 (~RE), U10.3 (DE); also elsewhere on the board
/ctrl/CMD/E78: R104.1, U11.2 (~RE), U11.3 (DE); also elsewhere on the board
/ctrl/CMD/L1: J3.12; also elsewhere on the board
/ctrl/CMD/L2: J3.10; also elsewhere on the board
GND: C17.2, C53.2, C54.2, C55.2, C56.2, C112.2, R17.2, R18.2, R31.2, R64.2, R67.2, R70.2, R73.2, R101.2, R102.2, R103.2, R104.2, U8.5 (GND), U9.5 (GND), U10.5 (GND), U11.5 (GND); also elsewhere on the board
GNDD: C17.1, J3.13, R31.1; also elsewhere on the board
unnamed: C53.1, C54.1, C55.1, C56.1, L7.1, R62.1, R65.1, R68.1, R71.1, U8.8 (VCC), U9.8 (VCC), U10.8 (VCC), U11.8 (VCC)
unnamed: J3.1, R62.2, R63.1, U8.6 (A)
unnamed: J3.2, R63.2, R64.1, U8.7 (B)
unnamed: J3.3, R65.2, R66.1, U9.6 (A)
unnamed: J3.4, P15.2, R69.2, R70.1, U10.7 (B)
unnamed: J3.5, P15.1, R68.2, R69.1, U10.6 (A)
unnamed: J3.6, R66.2, R67.1, U9.7 (B)
unnamed: J3.7, R71.2, R72.1, U11.6 (A)
unnamed: J3.8, R72.2, R73.1, U11.7 (B)
unnamed: J3.9, R18.1
unnamed: J3.11, R17.1
